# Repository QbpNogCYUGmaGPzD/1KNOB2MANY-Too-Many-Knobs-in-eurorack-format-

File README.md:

# 1knob2many

Original design by Tim Escobedo

This is an attempt to convert it to the eurorack format, with some changes to the design, to our taste. Mainly focused on driving percussion sounds, but YMMV.

Schematic and pcb by Koek en NMNN

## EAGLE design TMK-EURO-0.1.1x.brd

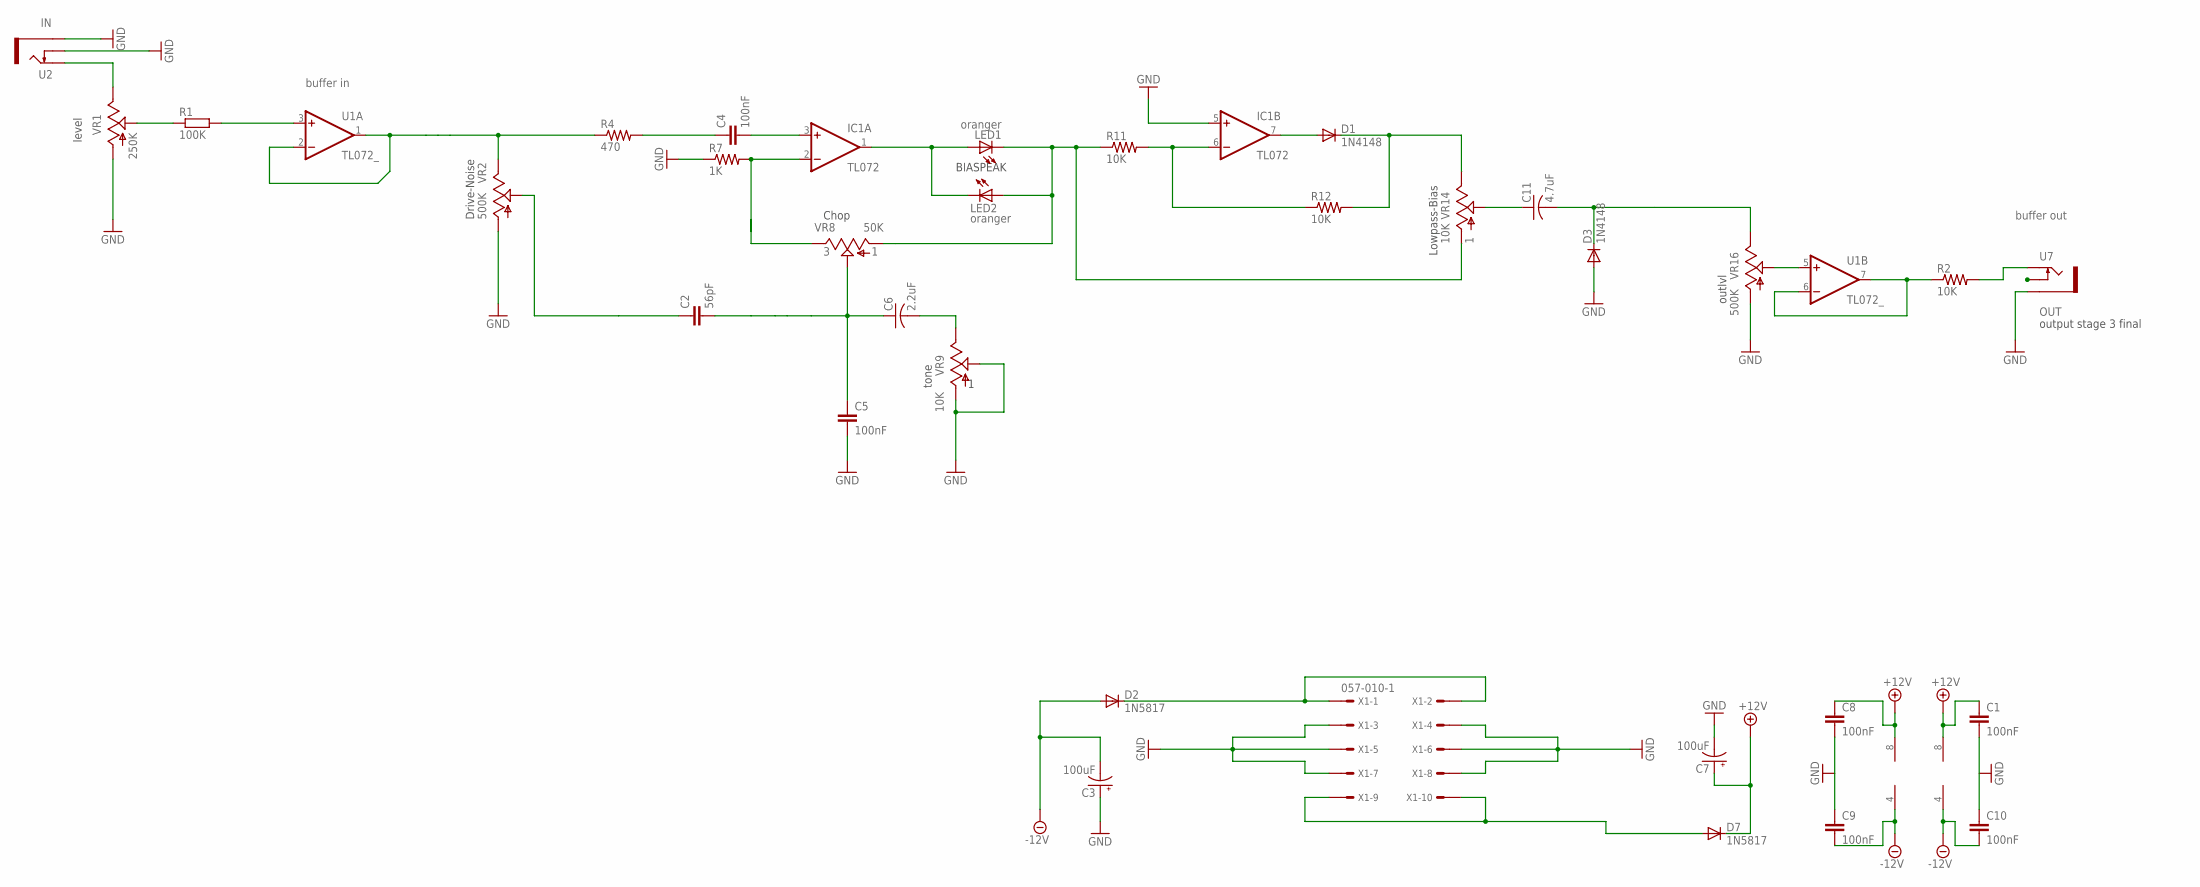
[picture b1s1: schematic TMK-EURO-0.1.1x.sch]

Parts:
C1, C4, C5, C8, C9, C10: 100nF; C050-035X075
C2: 56pF; C050-035X075
C3, C7: 100uF; 080_035
C6: 2.2uF; C050-030X075
C11: 4.7uF; C050-075X075
D1, D3: 1N4148; DO35-7
D2, D7: 1N5817; DO35-7
IC1: TL072; DIL08
LED1, LED2: oranger; LED3MM
R1: 100K; 7MM_RESISTOR
R2, R11, R12: 10K; 0207/7
R4: 470; 0207/7
R7: 1K; 0207/7
U1: TL072_; DIL08
U2: IN; THONKICONN
U7: THONKICONNOLD; THONKICONN
VR1: 250K; 9MM_SNAP-IN_POT
VR2, VR16: 500K; 9MM_SNAP-IN_POT
VR8: 50K; 9MM_SNAP-IN_POT
VR9, VR14: 10K; 9MM_SNAP-IN_POT
X1: 057-010-1

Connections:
+12V: C1.1, C7.+, C8.1, D7.C, IC1.8 (V+), U1.8 (V+)
-12V: C3.-, C9.2, C10.2, D2.A, IC1.4 (V-), U1.4 (V-)
GND: C3.+, C5.2, C7.-, D3.A, IC1.5 (+IN), R7.1, U2.P$1_SLEEVE (SLEEVE), U2.P$2_SWITCH (SWITCH), U7.P$1_SLEEVE (SLEEVE), VR1.1 (A), VR2.1 (A), VR9.1 (A), VR9.2 (S), VR16.1 (A), X1.3, X1.4, X1.5, X1.6, X1.7, X1.8
IN: U2.P$3_TIP (TIP), VR1.3 (E)
unnamed: R1.1, VR1.2 (S)
unnamed: D2.C, X1.1, X1.2
unnamed: C4.1, R4.2
unnamed: R1.2, U1.3 (+IN)
unnamed: C8.2, C9.1
unnamed: IC1.2 (-IN), R7.2, VR8.3 (E)
unnamed: LED1.K (C), LED2.A, R11.1, VR8.1 (A), VR14.1 (A)
unnamed: C6.2, VR9.3 (E)
unnamed: C2.1, VR2.2 (S)
unnamed: C1.2, C10.1
unnamed: C2.2, C5.1, C6.1, VR8.2 (S)
unnamed: IC1.6 (-IN), R11.2, R12.1
unnamed: D1.C, R12.2, VR14.3 (E)
unnamed: D1.A, IC1.7 (OUT)
unnamed: R2.2, U7.P$3_TIP (TIP)
unnamed: C11.1, VR14.2 (S)
unnamed: R4.1, U1.1 (OUT), U1.2 (-IN), VR2.3 (E)
unnamed: C11.2, D3.C, VR16.3 (E)
unnamed: C4.2, IC1.3 (+IN)
unnamed: R2.1, U1.6 (-IN), U1.7 (OUT)
unnamed: U1.5 (+IN), VR16.2 (S)
unnamed: IC1.1 (OUT), LED1.A, LED2.K (C)
unnamed: D7.A, X1.9, X1.10

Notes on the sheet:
OUT
level
Drive-Noise
Chop
BIASPEAK
tone
Lowpass-Bias
outlvl
output stage 3 final
buffer in
buffer out

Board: 2 copper layers, 34 parts (0 on the bottom side), 27 nets, no tracks yet.

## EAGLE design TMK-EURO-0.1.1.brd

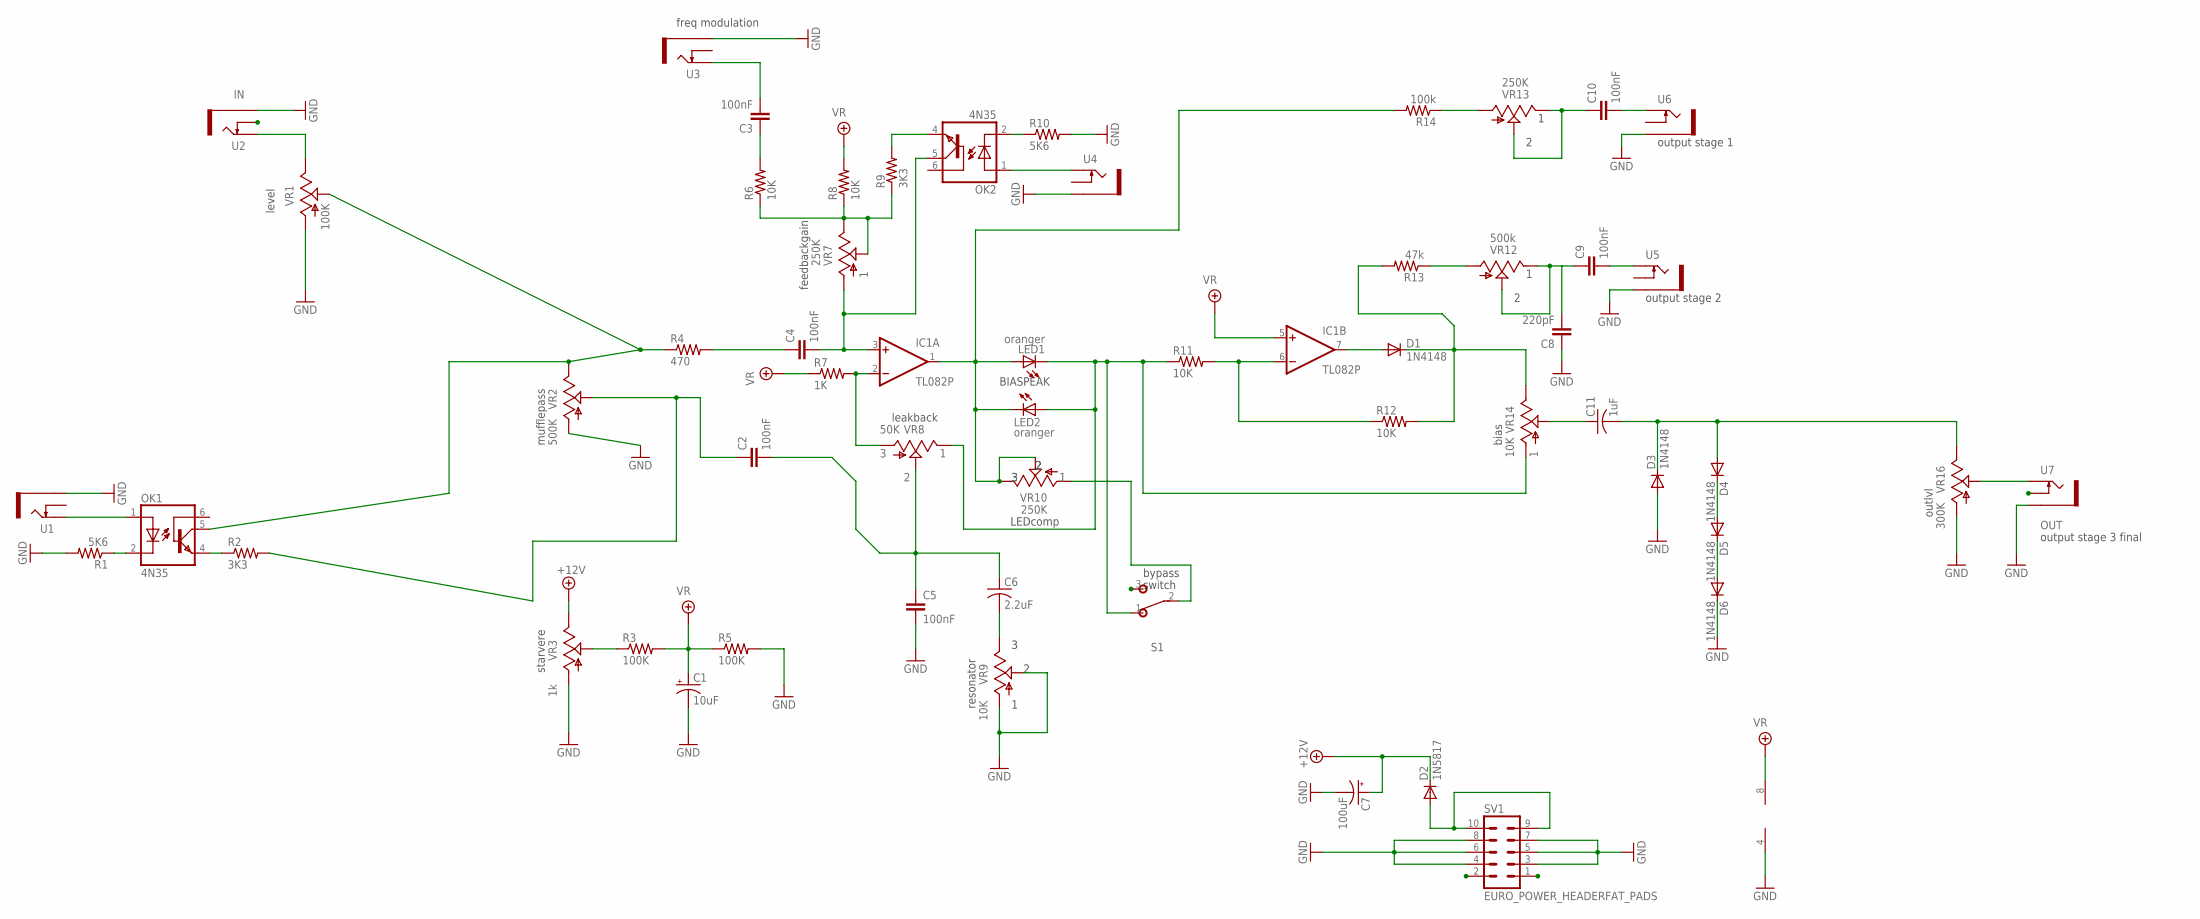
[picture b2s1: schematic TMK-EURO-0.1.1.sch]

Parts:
C1: 10uF; E2-5
C2, C3, C4, C5, C9, C10: 100nF; C050-035X075
C6: 2.2uF; C050-030X075
C7: 100uF; 080_035
C8: 220pF; C050-035X075
C11: 1uF; C050-075X075
D1, D3, D4, D5, D6: 1N4148; DO35-7
D2: 1N5817; DO35-7
IC1: TL082P; DIL08
LED1, LED2: oranger; LED3MM
OK1, OK2: 4N35; DIL06
R1, R10: 5K6; 0207/7
R2, R9: 3K3; 0207/7
R3, R5: 100K; 0207/7
R4: 470; 0207/7
R6, R8, R11, R12: 10K; 0207/7
R7: 1K; 0207/7
R13: 47k; 0207/7
R14: 100k; 0207/7
S1: SPDTPADS; SPDT
SV1: EURO_POWER_HEADERFAT_PADS; EURO_PWR_HEADER_FAT
U1, U2, U3, U4, U5, U6: IN; THONKICONN
U7: THONKICONNOLD; THONKICONN
VR1: 100K; 9MM_SNAP-IN_POT
VR2: 500K; 9MM_SNAP-IN_POT
VR3: 1k; 9MM_SNAP-IN_POT
VR7, VR10, VR13: 250K; 9MM_SNAP-IN_POT
VR8: 50K; 9MM_SNAP-IN_POT
VR9, VR14: 10K; 9MM_SNAP-IN_POT
VR12: 500k; 9MM_SNAP-IN_POT
VR16: 300K; 9MM_SNAP-IN_POT

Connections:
+12V: C7.+, D2.C, VR3.3 (E)
BYPASS: S1.2, VR10.1 (A)
GND: C1.-, C5.2, C7.-, C8.1, D3.A, D6.C, IC1.4 (V-), R1.2, R5.2, R10.2, SV1.3, SV1.4, SV1.5, SV1.6, SV1.7, SV1.8, U1.P$1_SLEEVE (SLEEVE), U2.P$1_SLEEVE (SLEEVE), U3.P$1_SLEEVE (SLEEVE), U4.P$1_SLEEVE (SLEEVE), U5.P$1_SLEEVE (SLEEVE), U6.P$1_SLEEVE (SLEEVE), U7.P$1_SLEEVE (SLEEVE), VR1.1 (A), VR2.1 (A), VR3.1 (A), VR9.1 (A), VR9.2 (S), VR16.1 (A)
IN: U2.P$3_TIP (TIP), VR1.3 (E)
unnamed: OK1.5 (COL), R4.1, VR1.2 (S), VR2.3 (E)
unnamed: C4.1, R4.2
unnamed: C4.2, IC1.3 (+IN), OK2.5 (COL), VR7.1 (A)
unnamed: R6.1, R8.1, R9.1, VR7.2 (S), VR7.3 (E)
unnamed: IC1.2 (-IN), R7.2, VR8.1 (A)
unnamed: LED1.K (C), LED2.A, R11.1, S1.1 (O), VR8.3 (E), VR14.1 (A)
unnamed: C6.2, VR9.3 (E)
unnamed: C2.1, R2.2, VR2.2 (S)
unnamed: IC1.1 (OUT), LED1.A, LED2.K (C), R14.2, VR10.2 (S), VR10.3 (E)
unnamed: C2.2, C5.1, C6.1, VR8.2 (S)
unnamed: IC1.6 (-IN), R11.2, R12.1
unnamed: D1.C, R12.2, R13.2, VR14.3 (E)
unnamed: D1.A, IC1.7 (OUT)
unnamed: D2.A, SV1.9, SV1.10
unnamed: C11.1, VR14.2 (S)
unnamed: U7.P$3_TIP (TIP), VR16.2 (S)
unnamed: C11.2, D3.C, D4.A, VR16.3 (E)
unnamed: D4.C, D5.A
unnamed: D5.C, D6.A
unnamed: R3.1, VR3.2 (S)
unnamed: C10.2, U6.P$3_TIP (TIP)
unnamed: R14.1, VR13.1 (A)
unnamed: OK2.4 (EMI), R9.2
unnamed: OK2.2 (C), R10.1
unnamed: R13.1, VR12.1 (A)
unnamed: OK2.1 (A), U4.P$3_TIP (TIP)
unnamed: OK1.4 (EMI), R2.1
unnamed: OK1.2 (C), R1.1
unnamed: OK1.1 (A), U1.P$3_TIP (TIP)
unnamed: C9.2, U5.P$3_TIP (TIP)
unnamed: C3.1, R6.2
unnamed: C3.2, U3.P$3_TIP (TIP)
OUTPUT1: C10.1, VR13.2 (S), VR13.3 (E)
OUTPUT2: C8.2, C9.1, VR12.2 (S), VR12.3 (E)
VR: C1.+, IC1.5 (+IN), IC1.8 (V+), R3.2, R5.1, R7.1, R8.2

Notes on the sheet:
OUT
level
feedbackgain
starvere
LEDcomp
mufflepass
leakback
BIASPEAK
switch
bypass
resonator
bias
outlvl
output stage 1
output stage 3 final
output stage 2
freq modulation

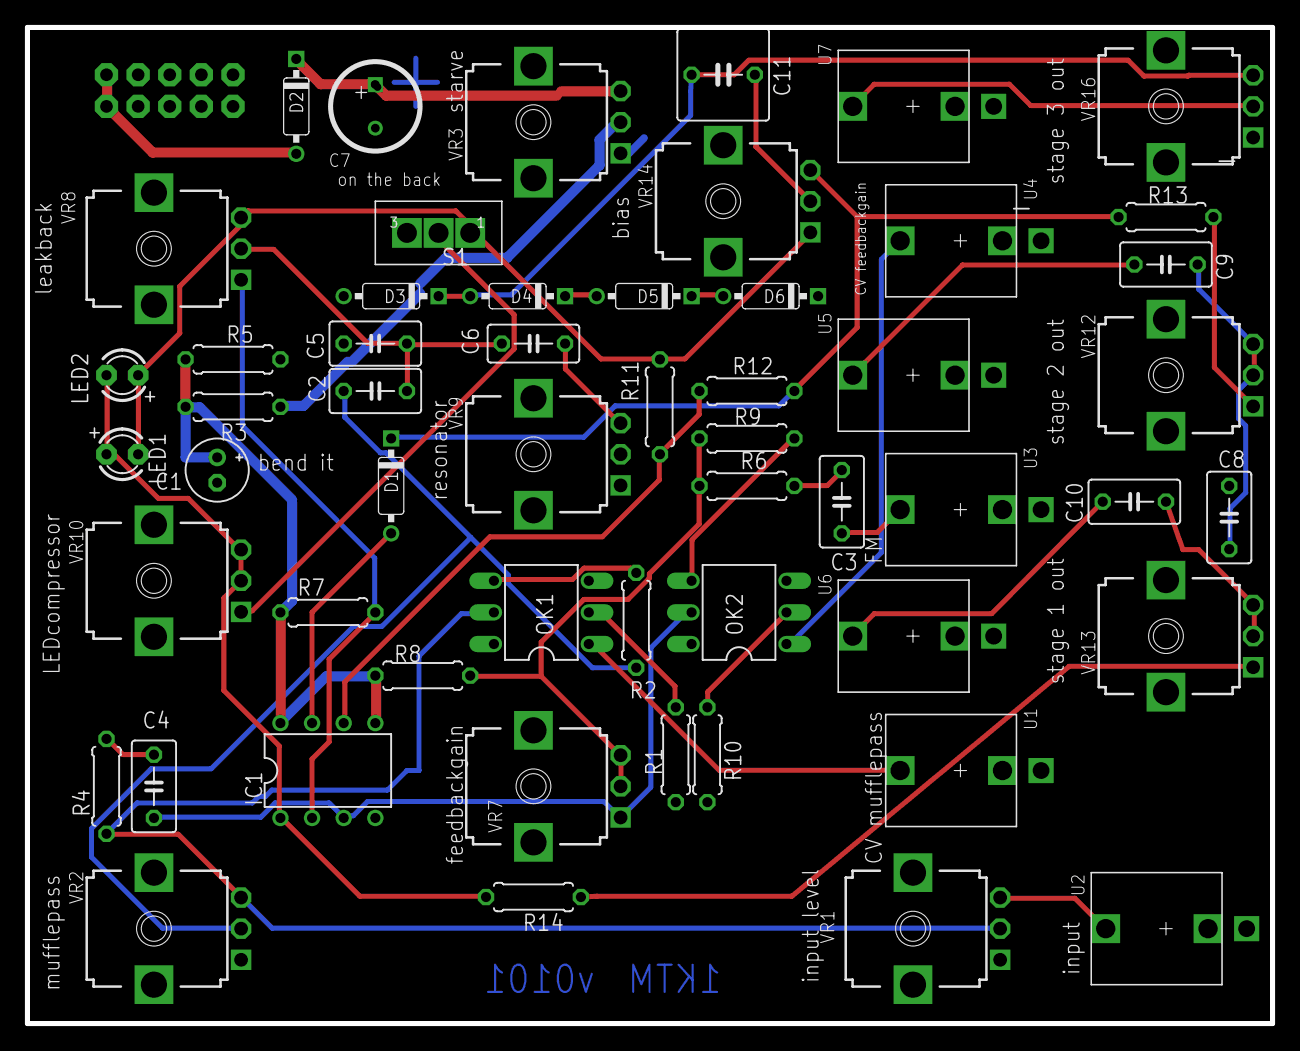
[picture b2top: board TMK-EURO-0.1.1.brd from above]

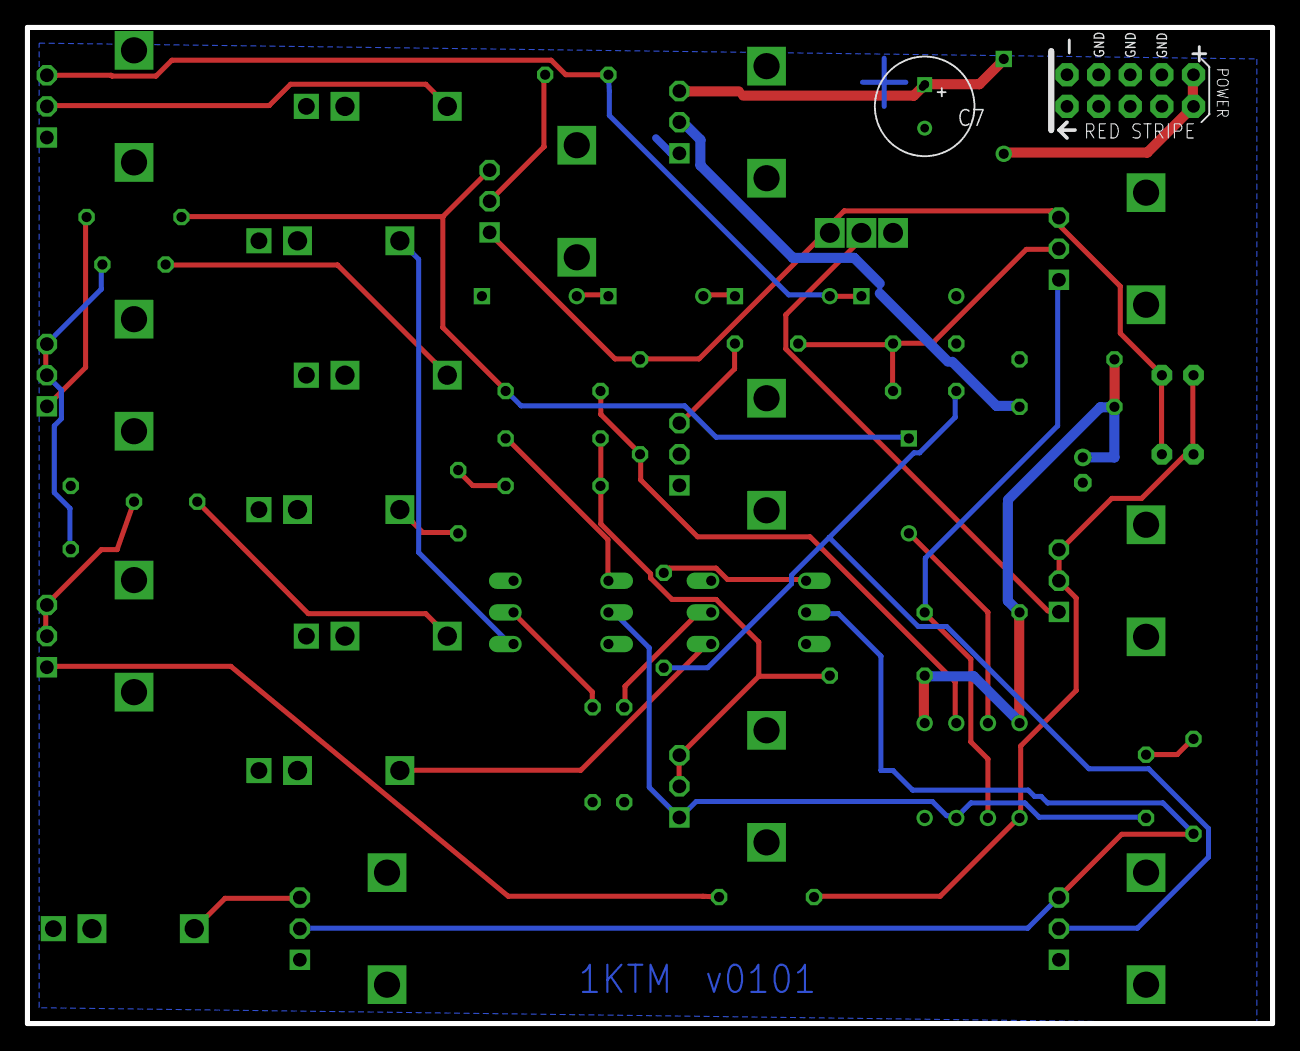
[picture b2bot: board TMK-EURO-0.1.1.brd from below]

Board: 2 copper layers, 100.0 x 80.0 mm, 56 parts (2 on the bottom side), 39 nets.

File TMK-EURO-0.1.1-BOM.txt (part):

Partlist exported from C:/Users/HADES/Documents/eagle/TMK-EURO/TMK-EURO-0.1.1.sch at 28-3-2017 5:23

Part Value                     Device                    Package             Description                                       DATA_SHEET                                                             MF                      MPN  OC_FARNELL OC_NEWARK
C1   10uF                      CPOL-USE2-5               E2-5                POLARIZED CAPACITOR, American symbol                                                                                                                                      
C2   100nF                     C-EU050-035X075           C050-035X075        CAPACITOR, European symbol                                                                                                                                                
C3   100nF                     C-EU050-035X075           C050-035X075        CAPACITOR, European symbol                                                                                                                                                
C4   100nF                     C-EU050-035X075           C050-035X075        CAPACITOR, European symbol                                                                                                                                                
C5   100nF                     C-EU050-035X075           C050-035X075        CAPACITOR, European symbol                                                                                                                                                
C6   2.2uF                     C-US050-030X075           C050-030X075        CAPACITOR, American symbol                                                                                                                                                
C7   100uF                     080                       080_035             47 - 470uF                                                                                                                                                                
C8   220pF                     C-EU050-035X075           C050-035X075        CAPACITOR, European symbol                                                                                                                                                
C9   100nF                     C-EU050-035X075           C050-035X075        CAPACITOR, European symbol                                                                                                                                                
C10  100nF                     C-EU050-035X075           C050-035X075        CAPACITOR, European symbol                                                                                                                                                
C11  1uF                       C-EU050-035X075           C050-035X075        CAPACITOR, European symbol                                                                                                                                                
D1   1N4148                    SMALL_DIODEDO35-7         DO35-7              Small Signal Diode                                                                                                                                                        
D2   1N5817                    SMALL_DIODEDO35-7         DO35-7              Small Signal Diode                                                                                                                                                        
D3   1N4148                    SMALL_DIODEDO35-7         DO35-7              Small Signal Diode                                                                                                                                                        
D4   1N4148                    SMALL_DIODEDO35-7         DO35-7              Small Signal Diode                                                                                                                                                        
D5   1N4148                    SMALL_DIODEDO35-7         DO35-7              Small Signal Diode                                                                                                                                                        
D6   1N4148                    SMALL_DIODEDO35-7         DO35-7              Small Signal Diode                                                                                                                                                        
IC1  TL082P                    TL082P                    DIL08               OP AMP                                            <a href="http://www.ti.com/lit/ds/symlink/tl084a.pdf"> Data sheet </a>                                                  
LED1 oranger                   LED3MM                    LED3MM              LED                                                                                                                                                                       
LED2 oranger                   LED3MM                    LED3MM              LED                                                                                                                                                                       
OK1  4N35                      4N35                      DIL06               MOTOROLA OPTO COUPLER                                                                                                    FAIRCHILD SEMICONDUCTOR 4N35 1328375    72K9946  
OK2  4N35                      4N35                      DIL06               MOTOROLA OPTO COUPLER                                                                                                    FAIRCHILD SEMICONDUCTOR 4N35 1328375    72K9946  
R1   5K6                       R-US_0207/7               0207/7              RESISTOR, American symbol                                                                                                                                                 
R2   3K3                       R-US_0207/7               0207/7              RESISTOR, American symbol                                                                                                                                                 
R3   100K                      R-US_0207/7               0207/7              RESISTOR, American symbol                                                                                                                                                 
R4   470                       R-US_0207/7               0207/7              RESISTOR, American symbol                                                                                                                                                 
R5   100K                      R-US_0207/7               0207/7              RESISTOR, American symbol                                                                                                                                                 
R6   10K                       R-US_0207/7               0207/7              RESISTOR, American symbol                                                                                                                                                 
R7   1K                        R-US_0207/7               0207/7              RESISTOR, American symbol                                                                                                                                                 
R8   10K                       R-US_0207/7               0207/7              RESISTOR, American symbol                                                                                                                                                 
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
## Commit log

2017-03-25 :circus_tent: Added .gitattributes & .gitignore files
2017-03-25 First setup
2017-03-25 Too Many Knobs
    Designed by Tim Escobedo. This is an attempt to convert it to the eurorack format.
2017-03-25 Make CC
2017-03-27 Final schematic design
    breadboard check
2017-03-27 naam
2017-03-28 v0101 PCB
2017-03-28 final design frontpanel include
2017-03-29 v0.1.0.1
    final V0101
    INcluded board., schematic en frontpanel pcb
2017-03-29 Added Libr
2017-04-06 Frontpsanel added
2017-04-06 Clean up
2017-09-27 huh?
2017-09-27 Cleanup for errors
    Removed all the CV-inputs. Fixed the power. Check this on breadboard
    first!
2017-09-27 Fixed power
    No Vr on power pin 8, but 12V from the main power supply
2017-09-27 Cleanup breadboard ready
2017-09-27 Nets netjes
2017-09-27 bom V1
2017-09-27 v1.1 schema only
2017-09-27 Buffers!
2017-10-01 Ready for breadboard v2
2017-10-01 Ground switch input jack
    Normal to groudn on input switch
2017-10-05 Buffered Euro Friendly
    Ready for tewaking and CV-inputs?
2017-10-05 Add 10k after attenuation
2017-10-15 Notes
2017-10-15 FinalCleanUp
    Ready for testing, adding CV
2018-01-07 Aanpassingen test
